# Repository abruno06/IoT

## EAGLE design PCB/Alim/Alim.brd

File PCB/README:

Will contain the PCB Eagle dump of the project

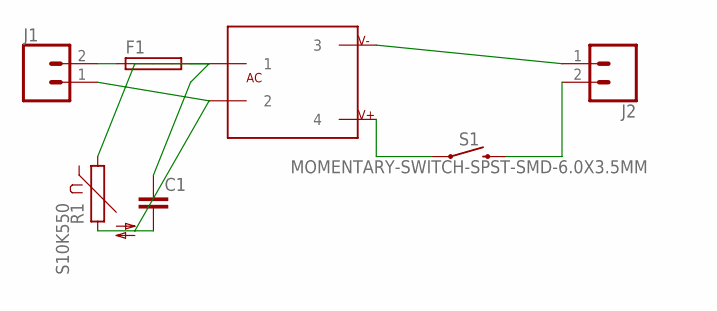
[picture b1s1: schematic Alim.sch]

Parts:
C1: C10/6; C10B6
F1: SHK20L
J1: CONN_025MM; SCREWTERMINAL-5MM-2
J2: CONN_02; 1X02
R1: S10K550
S1: MOMENTARY-SWITCH-SPST-SMD-6.0X3.5MM; TACTILE_SWITCH_SMD_6.0X3.5MM
U$1: HLK-PM03; HLK-PM

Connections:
unnamed: F1.1A, J1.2
unnamed: C1.1, F1.2A, R1.1, U$1.1
unnamed: J1.1, U$1.2
unnamed: J2.2, S1.2
unnamed: C1.2, R1.2
VC+: S1.1, U$1.4
VC-: J2.1, U$1.3

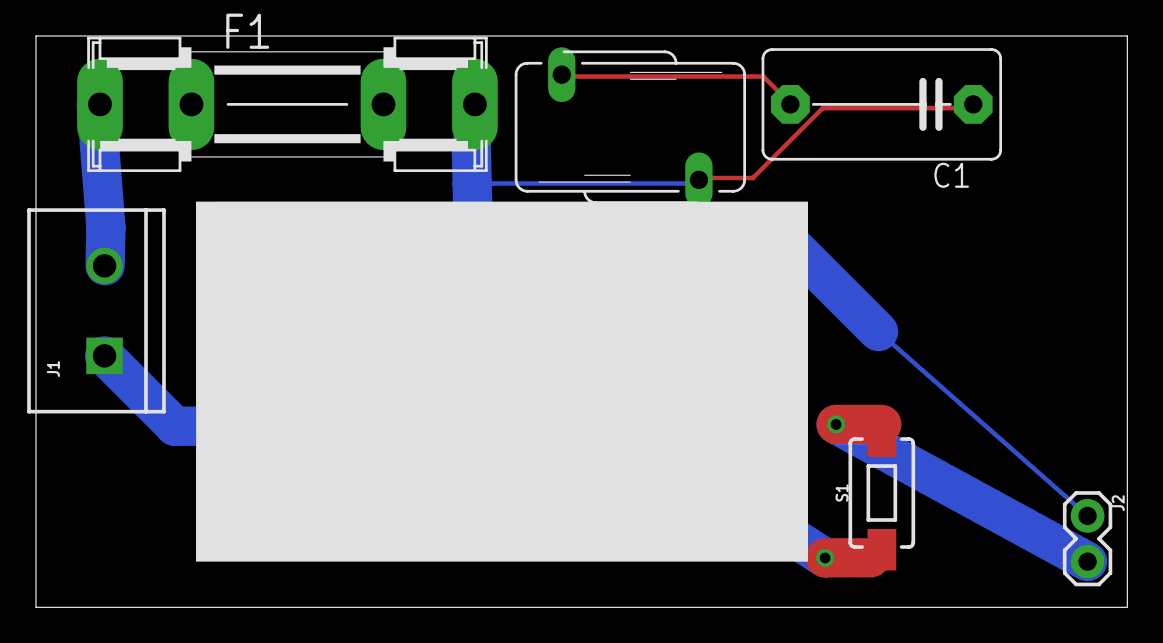
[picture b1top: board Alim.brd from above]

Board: 2 copper layers, 60.6 x 31.7 mm, 7 parts (0 on the bottom side), 7 nets.

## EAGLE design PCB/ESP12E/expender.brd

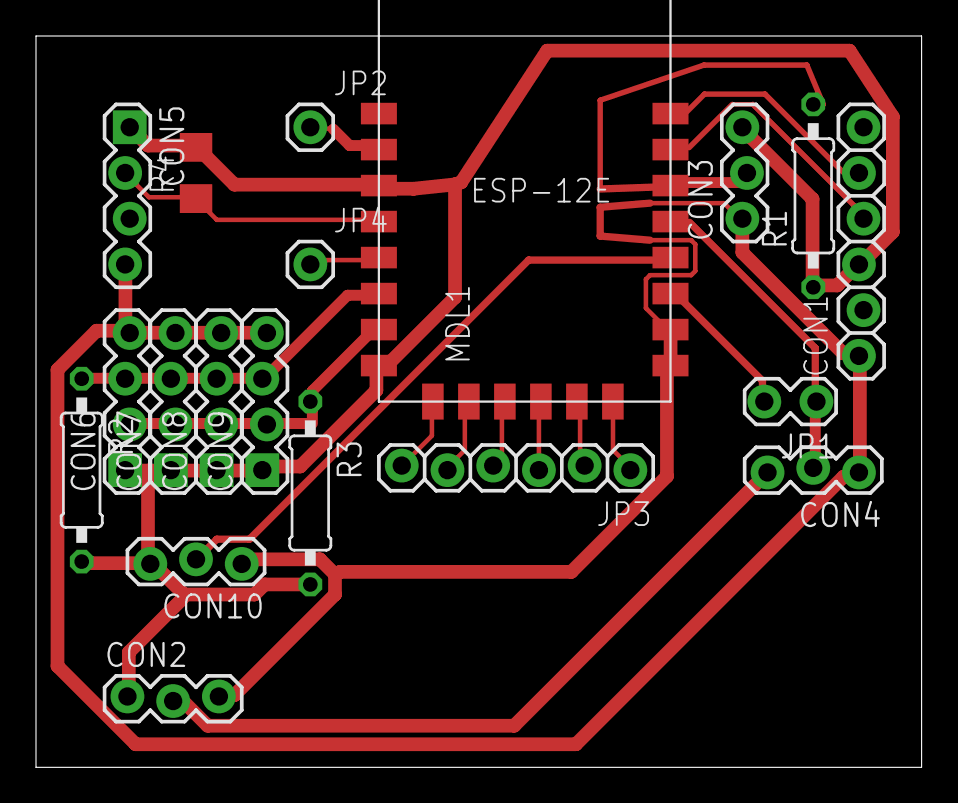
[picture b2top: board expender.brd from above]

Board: 2 copper layers, 49.2 x 40.6 mm, 19 parts (0 on the bottom side), 20 nets.

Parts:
CON1: SERIAL; 1X06_LOCK
CON2: PWD; 1X03_LOCK
CON3: DLS; 1X03_LOCK
CON4: IR; 1X03_LOCK
CON5: DHT11; 1X04_LOCK
CON6: I2C1; 1X04_LOCK
CON7: I2C2; 1X04_LOCK
CON8: I2C3; 1X04_LOCK
CON9: I2C4; 1X04_LOCK
CON10: FIRM; 1X03_LOCK
JP1: M02LOCK; 1X02_LOCK
JP2, JP4: M01PTH; 1X01
JP3: 1X06_LOCK
MDL1: ESP8266-ESP12E
R1: 4.7K; 0207/10
R2, R3: 10K; 0207/10
R4: 4.7K; R1206

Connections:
GND: CON1.1, CON2.3, CON3.1, CON4.1, CON5.4, CON6.4, CON7.4, CON8.4, CON9.4, CON10.1, MDL1.9, MDL1.10
unnamed: CON5.2, MDL1.4, R4.1
unnamed: CON3.2, MDL1.14, R1.2
unnamed: CON10.2, MDL1.12
unnamed: CON2.2, CON4.3
unnamed: JP4.1, MDL1.5
unnamed: JP1.2, MDL1.11
unnamed: CON4.2, JP1.1, MDL1.13
unnamed: JP2.1, MDL1.2
unnamed: JP3.2, MDL1.17
unnamed: JP3.6, MDL1.18
unnamed: JP3.5, MDL1.19
unnamed: JP3.1, MDL1.20
unnamed: JP3.4, MDL1.21
unnamed: JP3.3, MDL1.22
unnamed: CON1.5, MDL1.16
unnamed: CON1.4, MDL1.15
SDA: CON6.2, CON7.2, CON8.2, CON9.2, MDL1.7, R3.1
SDL: CON6.3, CON7.3, CON8.3, CON9.3, MDL1.6, R2.1
VCC+3V: CON1.3, CON2.1, CON3.3, CON5.1, CON6.1, CON7.1, CON8.1, CON9.1, CON10.3, MDL1.3, MDL1.8, R1.1, R2.2, R3.2, R4.2

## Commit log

2016-04-23 original repo
2016-04-23 Add node-red docker engine
2016-04-23 static configuration
2016-04-23 Add ESP8266 and PCB information
2016-04-23 fix typo on the node-red Dockerfile
2016-04-23 Added files via upload
2016-04-23 change directory
2016-04-23 recreate the directory ESP12E
2016-05-01 Add nodered for raspberry B+
2016-05-01 update the comment on the static.js file to indicate the change that has been done
2016-05-01 remove empy line on the Dockerfile
2016-05-29 Add node_red Dockerfile and Makefile for Node Red based on Alpine container
2016-05-29 Add node_red Dockerfile and Make file base on node_red_base_alpine adding couple of usefull module for IoT
2016-05-29 Origin/v0.0.0 (#3)
    * Add node_red Dockerfile and Makefile for Node Red based on Alpine container
    * Add node_red Dockerfile and Make file base on node_red_base_alpine adding couple of usefull module for IoT
2016-05-29 Add Makefile to build the nodered container into RPI
2016-05-29 Add consul,ceph,nginx
2016-05-29 change on the node-red Dockerfile
2016-05-29 change on RPI
2016-05-29 update the RPI NR Makefile
2016-05-29 remove node-red into RPI
2017-01-02 Add nodered dashboard
2020-01-04 To remove Backup file
2020-01-04 Add gitignore to avoid json files been pushed
2020-01-04 remove lua files as deprecated
2020-01-04 Add mcp23xx.py file with CR
2020-01-04 mycropython code added
2020-01-04 update git ignore
2020-01-04 add boot and update readme
2020-01-04 read me update
2020-01-04 remove backup files
2020-01-04 full update
2020-01-04 Add detail
2020-01-04 Add more detail
2020-01-04 fix bug
2020-01-04 more to read
2020-01-04 more doc
2020-01-12 update the wifi to be able to change wifi between boot and run. Allow dhcp hostname setting
2020-01-12 chqnge boot to machine.reset model to clean all and restart from boot
2020-01-12 add mcp capability
2020-01-12 update and add sensors class
2020-01-12 complete mcp initialization
2020-01-12 update documentation for mcp
2020-01-12 update capabilities checking
2020-01-12 update capabilities
2020-01-12 mcp input checking and set
2020-01-12 add input name for mcp and set capability
2020-01-12 tests read
2020-01-12 set mcp checking
2020-01-12 display status
2020-01-12 fix bug in the set
2020-01-12 set mcp working
2020-01-12 set one mcp port completed
2020-01-12 update the documentation
2020-01-12 mcp topics modify
2020-01-12 update doc
2020-01-12 format doc
2020-01-12 update gitignore
2020-01-12 code cleaning
2020-01-12 add ds18b20
2020-01-12 fix typo on ds18b20
2020-01-12 fix module name ds18b20
2020-01-12 fix module name ds18x20
2020-01-12 all work for ds18b20
2020-01-18 add command on the doc
2020-01-18 doc update
2020-01-18 doc change
2020-01-18 doc ref update
2020-01-18 ref update
2020-01-19 test
2020-01-19 decde the data
2020-01-19 ota is working but unsafe
2020-01-19 activate webrepl
2020-10-17 update the feature
2020-10-17 more documentation
2020-10-17 update the doc
2020-10-25 many change for more stability
2020-10-28 add oled
2020-10-29 boot.json wifi is replcaed by config.wifi to have device rebooting on last known wifi rather than boot.json one
2020-10-31 fix some bug
2020-10-31 desactivate the exception if ssd1306 not activated
2020-11-22 add bme280 initial code
2021-04-11 Add support of micropython v1.14 and veml6070 using adafruit .py module
2022-03-14 update dockerfile
2022-03-14 update dockerfiles
2022-10-09 save
2022-10-15 remove .mpy from .gitignore
2022-10-15 introduce the dynamic call
2022-10-15 Add more dynamic and capability : before cutoff
2022-10-15 one more step to actions.json file
2022-10-15 move to new micropython import style
2022-10-15 code rework
2022-10-15 updated version with beta remote fct call
2022-10-15 add code comment :-)
2022-10-15 Working code
2022-10-15 code cleaning start again
2022-10-16 with the change
2022-10-16 with make file to rebuild
2022-10-16 add actions-init to save data
2022-10-16 save the enhancement
2022-10-16 saving
2022-10-16 cleaning
2022-10-16 save mpy
2022-10-16 working as expected, need doc update
2022-10-17 night work save
2022-10-17 last one
2022-10-18 bit more stable almost there
2022-10-18 few cleaning
2022-10-20 code optimization attempt 1
2022-10-21 optimize memory
2022-11-12 fix and clean
2022-11-12 fix and cleaning
2022-11-12 add network timer
2022-11-12 enhance
2022-11-12 save code cleaning
2022-11-12 sonar cleaning
2022-11-13 recompile
2022-11-13 enhanced
2022-11-13 enhancement
2022-11-19 enhance and ceaning

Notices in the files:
parts and their libraries:
SparkFun-Connectors: Licensing: Creative Commons ShareAlike 4.0 International - https://creativecommons.org/licenses/by-sa/4.0
